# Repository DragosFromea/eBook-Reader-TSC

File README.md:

| Component               | Supplier Link                                                                 | Datasheet                                                                 |
|-------------------------|-------------------------------------------------------------------------------|---------------------------------------------------------------------------|
| 112A-TAAR-R03 ATTEND    | -| [Datasheet](https://www.snapeda.com/parts/112A-TAAR-R03/Attend/datasheet/)|
| BD5229G-TR              | [Mouser](https://www.mouser.co.uk/ProductDetail/ROHM-Semiconductor/BD5229G-TR?qs=4kLU8WoGk0vvnhrrYwdszw%3D%3D)| [Datasheet](https://fscdn.rohm.com/en/products/databook/datasheet/ic/power/voltage_detector/bd52xxg-e.pdf) |
| CPH3225A (Supercapacitor)| [SnapEDA](https://www.snapeda.com/parts/CPH3225A/Seiko+Instruments/view-part/?ref=eda) | [Datasheet](https://www.snapeda.com/parts/CPH3225A/Seiko%20Instruments/datasheet/) |
| DS3231SN# (RTC)         | [SnapEDA](https://www.snapeda.com/parts/DS3231SN%23/Analog+Devices/view-part/?ref=eda) | [Datasheet](https://www.analog.com/media/en/technical-documentation/data-sheets/DS3231.pdf) |
| ESP32-C6-WROOM-1-N8     | [SnapEDA](https://www.snapeda.com/parts/ESP32-C6-WROOM-1-N8/Espressif+Systems/view-part/?ref=eda) | [Datasheet](https://www.espressif.com/sites/default/files/documentation/esp32-c6-wroom-1_datasheet_en.pdf) |
| FH34SRJ-24S-0.5SH99     | [Mouser](https://ro.mouser.com/ProductDetail/Hirose-Connector/FH34SRJ-24S-0.5SH99?qs=vcbW%252B4%252BSTIpKBl5ap9J8Fw%3D%3D) | [Datasheet](https://www.hirose.com/product/document?clcode=CL0537-0513-9-10&productname=FH34SRJ-24S-0.5SH(99)&series=FH34&documenttype=Catalog&lang=en&documentid=D31688_en) |
| MBR0530 (Schottky Diode)| [SnapEDA](https://www.snapeda.com/parts/MBR0530/Onsemi/view-part/?ref=eda)                 | [Datasheet](https://www.onsemi.com/pdf/datasheet/mbr0530-d.pdf)           |
| MAX17048G+T10 (Fuel Gauge)| [SnapEDA](https://www.snapeda.com/parts/MAX17048G+T10/Analog+Devices/view-part/?ref=eda)| [Datasheet](https://www.analog.com/media/en/technical-documentation/data-sheets/MAX17048-MAX17049.pdf) |
| USBLC6-2SC6Y (TVS Diode)| [SnapEDA](https://www.snapeda.com/parts/USBLC6-2SC6Y/STMicroelectronics/view-part/?ref=eda)| [Datasheet](https://www.st.com/resource/en/datasheet/usblc6-2.pdf) |
| W25Q512JVEIQ (Flash)    | [SnapEDA](https://www.snapeda.com/parts/W25Q512JVEIQ/Winbond+Electronics/view-part/?ref=eda)| [Datasheet](https://www.winbond.com/resource-files/W25Q512JV%20SPI%20RevB%2006252019%20KMS.pdf) |
| XC6220A331MR-G (LDO)    | [Mouser](https://www.mouser.co.uk/ProductDetail/Torex-Semiconductor/XC6220A331MR-G?qs=AsjdqWjXhJ8ZSWznL1J0gg%3D%3D)| [Datasheet](https://product.torexsemi.com/system/files/series/xc6220.pdf) |                                                                         |
| QWIIC Connector          | -                           | [Datasheet](https://learn.sparkfun.com/tutorials/qwiic-shield-for-arduino--photon-hookup-guide) |

Core Components
Microcontroller (ESP32-C6-WROOM-1-N8):

    Architecture: 32-bit RISC-V

    Clock Speed: 160 MHz

    Wireless: Wi-Fi 6 (2.4 GHz), Bluetooth 5.0

    Functions: System control, sensor/module communication, power management.

Power Management
Battery System:

    Type: Li-Po (Lithium Polymer)

    Capacity: 3.7V, 1800mAh

    Charging Circuit: MCP73831T (5V input via USB-C)

    Protection: Overcharge and deep discharge safeguards.

    Voltage Regulation: LDO regulator (stable 3.3V output).

Storage & Display
E-Paper Display:

    Size: 7.5 inches | Resolution: 800×480 pixels

    Interface: SPI

MicroSD Card Module:

    Format: FAT32 | Interface: SPI

External NOR Flash:

    Capacity: 64MB | Interface: SPI

Sensors & Timing
Environmental Sensor (BME688):

    Metrics: Temperature, humidity, air pressure, gas levels.

    Interface: I2C

Real-Time Clock (DS3231SN):

    Function: Maintains time/date during power loss.

    Interface: I2C

User Interface
USB-C Connector:

    Role: Power input, data transfer.

    Safety: ESD protection + Schottky diode (reverse polarity).

Tactile Push Buttons:

    Control: GPIO-based input.

Communication Interfaces
SPI: SD card, external flash, e-paper display.

I2C: BME688 sensor, DS3231SN RTC.

GPIO: Button controls, general I/O.

UART: Debugging, serial communication.

Wireless: Wi-Fi 6/Bluetooth 5.0 (via ESP32-C6).

### Power Consumption Estimation  
| Component                      | Current Draw (mA) | Voltage (V) | Power (mW) |  
|--------------------------------|-------------------|-------------|------------|  
| ESP32-C6 (Wi-Fi active)        | 200               | 3.3         | 660        |  
| E-Paper Display (Updating)     | 40                | 3.3         | 132        |  
| BME688 Sensor (Measuring)      | 3.1               | 3.3         | 10.23      |  
| RTC Module (Active)            | 0.15              | 3.3         | 0.495      |  
| SD Card (Active)               | 50                | 3.3         | 165        |  
| External NOR Flash             | 25                | 3.3         | 82.5       |  
| **Total Estimated Power Consumption** | **~318.5 mA**     | **3.3**     | **1050.72**|  

---

### ESP32-C6 Pin Mapping  
| Component                      | ESP32-C6 Pin(s)                                | Interface | Purpose                                                                 |  
|--------------------------------|------------------------------------------------|-----------|-------------------------------------------------------------------------|  
| E-Paper Display                | IO7 (MOSI), IO6 (SCK), IO10 (CS), IO5 (DC), IO23 (RST), IO3 (BUSY) | SPI       | Transfers image data to the display and controls its state.             |  
| MicroSD Card                   | IO7 (MOSI), IO6 (SCK), IO4 (SS_SD), IO2 (MISO) | SPI       | Storage and retrieval of e-book files.                                  |  
| Environmental Sensor (BME688)  | IO21 (SDA), IO22 (SCL)                         | I2C       | Reads temperature, humidity, pressure, and air quality data.            |  
| RTC Module (DS3231)            | IO21 (SDA), IO22 (SCL), IO18 (RST), IO1 (32KHz), IO0 (INT_RTC) | I2C       | Maintains time/date tracking during system power-off.                   |  
| External NOR Flash             | IO11 (CS), IO6 (SCK), IO2 (MISO), IO7 (MOSI)   | SPI       | Additional storage for application data.                                |  
| Battery Monitoring             | IO21 (SDA), IO22 (SCL)                         | I2C       | Monitors battery voltage and charge status.                             |  
| USB-C Connection               | GPIOs (via voltage regulation)                 | USB       | Powers and programs the ESP32-C6.                                       |  
| Control Buttons                | IO9 (BOOT), IO15 (CHANGE), EN (RESET)          | GPIO      | User input for device interactions (boot, mode change, reset).          |  

Am acceptat erorile SMD de overlap

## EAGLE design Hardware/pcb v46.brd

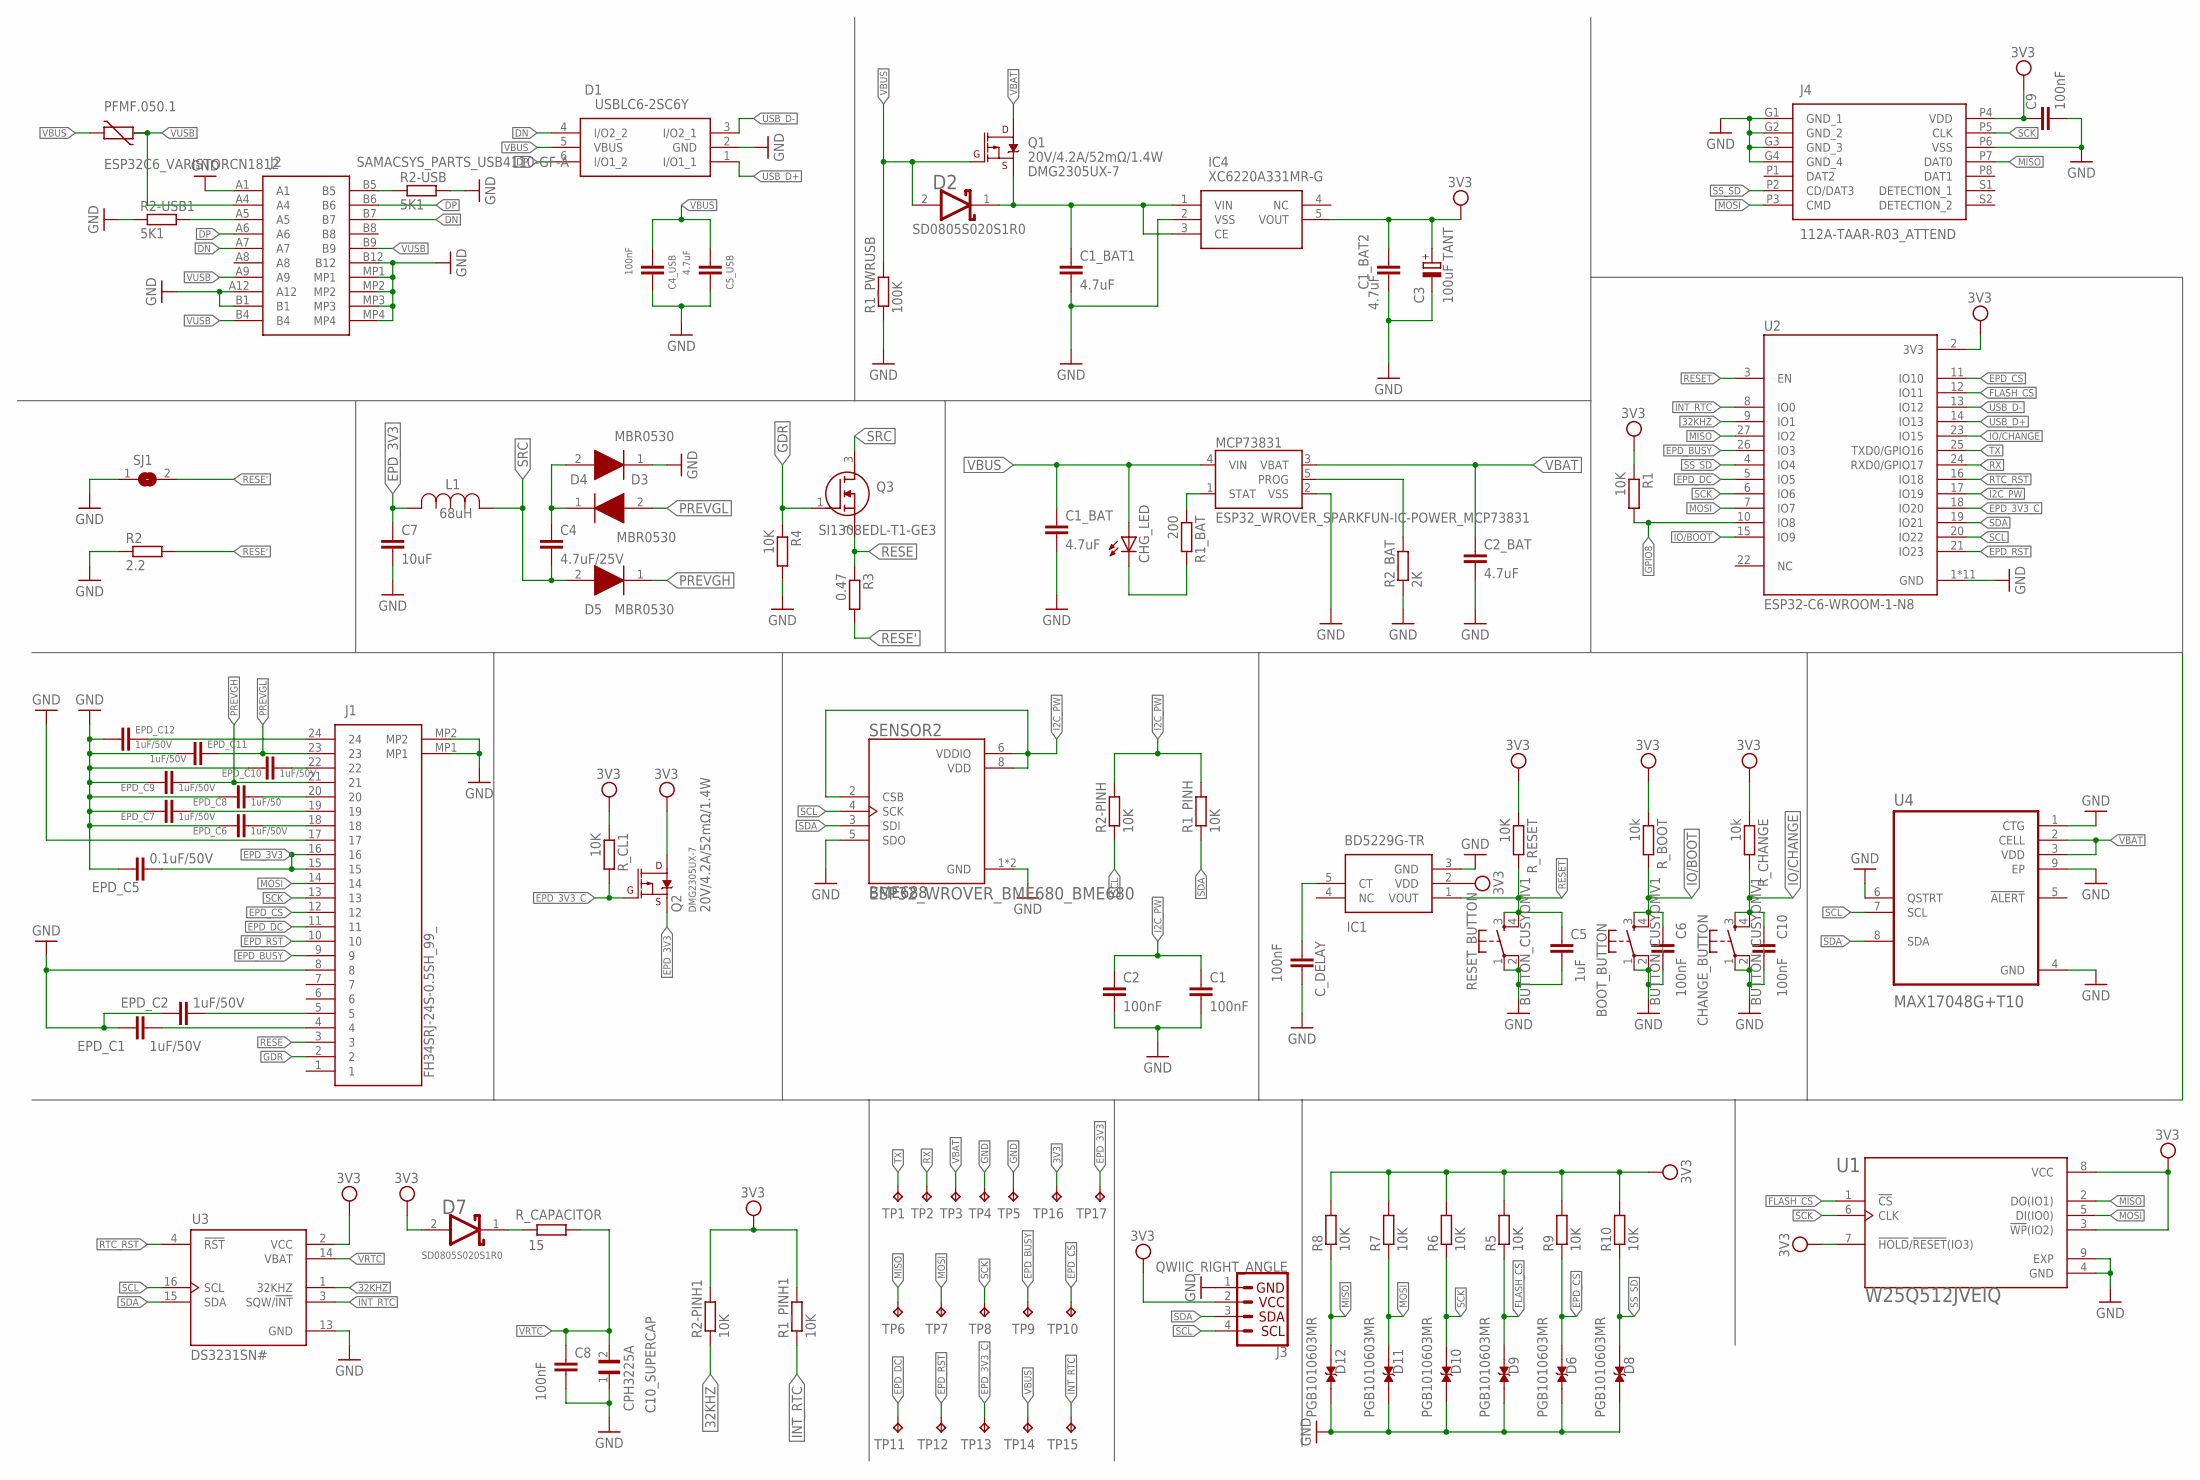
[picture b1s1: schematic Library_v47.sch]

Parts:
BOOT_BUTTON: BUTTON_CUSYOMV1; MYBUTTON
C1, C2, C4_USB, C6, C8, C9, C10: 100nF; ESP32_WROVER_EAGLE-LTSPICE_C0402
C1_BAT, C1_BAT1, C1_BAT2, C2_BAT, C5_USB: 4.7uF; ESP32_WROVER_EAGLE-LTSPICE_C0402
C3: 100uF TANT; RCL_CT3528
C4: 4.7uF/25V; ESP32_WROVER_EAGLE-LTSPICE_C0402
C5: 1uF; ESP32_WROVER_EAGLE-LTSPICE_C0402
C7: 10uF; ESP32_WROVER_EAGLE-LTSPICE_C0402
C10_SUPERCAP: CPH3225A; CAPCP3225X100N
CHANGE_BUTTON: BUTTON_CUSYOMV1; MYBUTTON
CHG_LED: ADAFRUIT_LEDCHIP-LED0603; ADAFRUIT_CHIP-LED0603
C_DELAY: 100nF; ESP32_WROVER_EAGLE-LTSPICE_C0402
D1: USBLC6-2SC6Y; SOT95P280X145-6N
D2, D7: ESP32_WROVER_AVX---SD0805S020S1R0_AVX_SD0805S020S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; ESP32_WROVER_AVX---SD0805S020S1R0_AVX_SD0805S020S1R0_0
D3, D4, D5: MBR0530; SOD3716X135N
D6, D8, D9, D10, D11, D12: PGB1010603MR; DIOC1608X36N
EPD_C1, EPD_C2, EPD_C6, EPD_C7, EPD_C9, EPD_C10, EPD_C11, EPD_C12: 1uF/50V; ESP32_WROVER_EAGLE-LTSPICE_C0402
EPD_C5: 0.1uF/50V; ESP32_WROVER_EAGLE-LTSPICE_C0402
EPD_C8: 1uF/50; ESP32_WROVER_EAGLE-LTSPICE_C0402
IC1: BD5229G-TR; SOT95P280X125-5N
IC4: XC6220A331MR-G; SOT95P280X120-5N
J1: FH34SRJ-24S-0.5SH_99_; FH34SRJ24S05SH99
J2: SAMACSYS_PARTS_USB4110-GF-A; SAMACSYS_PARTS_USB4110GFA
J3: QWIIC_RIGHT_ANGLE; JST04_1MM_RA
J4: 112A-TAAR-R03_ATTEND; 112ATAARR03ATTEND
L1: 68uH; IND_4828-WE-TPC_WRE
MCP73831: ESP32_WROVER_SPARKFUN-IC-POWER_MCP73831; ESP32_WROVER_SPARKFUN-IC-POWER_SOT23-5
PFMF.050.1: ESP32C6_VARISTORCN1812; ESP32C6_VARISTOR_CT/CN1812
Q1, Q2: 20V/4.2A/52mΩ/1.4W; ESP32_WROVER_SPARKFUN-DISCRETESEMI_SOT23-3
Q3: SI1308EDL-T1-GE3; SOT65P210X110-3N
R1, R1_PINH, R1_PINH1, R2-PINH, R2-PINH1, R4, R5, R6, R7, R8, R9, R10: 10K; ESP32_WROVER_EAGLE-LTSPICE_R0402
R1_BAT: 200; ESP32_WROVER_EAGLE-LTSPICE_R0402
R1_PWRUSB: 100K; ESP32_WROVER_EAGLE-LTSPICE_R0402
R2: 2.2; ESP32_WROVER_EAGLE-LTSPICE_R0402
R2-USB, R2-USB1: 5K1; ESP32_WROVER_EAGLE-LTSPICE_R0402
R2_BAT: 2K; ESP32_WROVER_EAGLE-LTSPICE_R0402
R3: 0.47; ESP32_WROVER_EAGLE-LTSPICE_R0402
RESET_BUTTON: BUTTON_CUSYOMV1; MYBUTTON
R_BOOT: 10k; ESP32_WROVER_EAGLE-LTSPICE_R0402
R_CAPACITOR: 15; ESP32_WROVER_EAGLE-LTSPICE_R0402
R_CHANGE: 10k; ESP32_WROVER_EAGLE-LTSPICE_R0402
R_CL1: 10K; ESP32_WROVER_EAGLE-LTSPICE_R0402
R_RESET: 10K; ESP32_WROVER_EAGLE-LTSPICE_R0402
SENSOR2: ESP32_WROVER_BME680_BME680; ESP32_WROVER_BME680_PSON80P300X300X100-8N
SJ1: SJ
TP1, TP2, TP3, TP4, TP5, TP6, TP7, TP8, TP9, TP10, TP11, TP12, TP13, TP14, TP15, TP16, TP17: TPTP20R; TP20R
U1: W25Q512JVEIQ; SON127P600X800X80-9N
U2: ESP32-C6-WROOM-1-N8; XCVR_ESP32-C6-WROOM-1-N8
U3: DS3231SN#; SOIC127P1032X265-16N
U4: MAX17048G+T10; SON50P200X200X80-9N

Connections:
3V3: C1_BAT2.1, C3.+, C9.1, D7.2 (ANODE), IC1.2 (VDD), IC4.5 (VOUT), J3.2, J4.P4 (VDD), Q2.3 (D), R1.1, R1_PINH1.2, R2-PINH1.2, R5.2, R6.2, R7.2, R8.2, R9.2, R10.2, R_BOOT.1, R_CHANGE.1, R_CL1.1, R_RESET.1, TP16.TP, U1.3 (!WP!(IO2)), U1.7 (!HOLD!/!RESET!(IO3)), U1.8 (VCC), U2.2 (3V3), U3.2 (VCC)
32KHZ: R2-PINH1.1, U2.9 (IO1), U3.1 (32KHZ)
DN: D1.4 (I/O2_2), J2.A7, J2.B7
DP: D1.6 (I/O1_2), J2.A6, J2.B6
EPD_3V3: C7.1, EPD_C5.1, J1.15, J1.16, L1.2, Q2.2 (S), TP17.TP
EPD_3V3_C: Q2.1 (G), R_CL1.2, TP13.TP, U2.18 (IO20)
EPD_BUSY: J1.9, TP9.TP, U2.26 (IO3)
EPD_CS: D6.2, J1.12, R9.1, TP10.TP, U2.11 (IO10)
EPD_DC: J1.11, TP11.TP, U2.5 (IO5)
EPD_RST: J1.10, TP12.TP, U2.21 (IO23)
FLASH_CS: D9.2, R5.1, U1.1 (!CS), U2.12 (IO11)
GDR: J1.2, Q3.1 (G), R4.1
GND: BOOT_BUTTON.1, BOOT_BUTTON.2, C1.2, C1_BAT.2, C1_BAT1.2, C1_BAT2.2, C2.2, C2_BAT.2, C3.-, C4_USB.2, C5.2, C5_USB.2, C6.2, C7.2, C8.2, C9.2, C10.2, C10_SUPERCAP.1, CHANGE_BUTTON.1, CHANGE_BUTTON.2, C_DELAY.2, D1.2 (GND), D4.1 (K), D6.1, D8.1, D9.1, D10.1, D11.1, D12.1, EPD_C1.2, EPD_C2.2, EPD_C5.2, EPD_C6.2, EPD_C7.2, EPD_C8.2, EPD_C9.2, EPD_C10.2, EPD_C11.2, EPD_C12.2, IC1.3 (GND), IC4.2 (VSS), J1.8, J1.17, J1.MP1, J1.MP2, J2.A1, J2.A12, J2.B1, J2.B12, J2.MP1, J2.MP2, J2.MP3, J2.MP4, J3.1, J4.G1 (GND_1), J4.G2 (GND_2), J4.G3 (GND_3), J4.G4 (GND_4), J4.P6 (VSS), MCP73831.2 (VSS), R1_PWRUSB.1, R2.1, R2-USB.2, R2-USB1.1, R2_BAT.1, R4.2, RESET_BUTTON.1, RESET_BUTTON.2, SENSOR2.1 (GND), SENSOR2.5 (SDO), SENSOR2.7 (GND), SJ1.1, TP4.TP, TP5.TP, U1.4 (GND), U1.9 (EXP), U2.1 (GND), U2.28 (GND), U2.29_1 (GND), U2.29_2 (GND), U2.29_3 (GND), U2.29_4 (GND), U2.29_5 (GND), U2.29_6 (GND), U2.29_7 (GND), U2.29_8 (GND), U2.29_9 (GND), U3.13 (GND), U4.1 (CTG), U4.4 (GND), U4.6 (QSTRT), U4.9 (EP)
GPIO8: R1.2, U2.10 (IO8)
I2C_PW: C1.1, C2.1, R1_PINH.2, R2-PINH.2, SENSOR2.2 (CSB), SENSOR2.6 (VDDIO), SENSOR2.8 (VDD), U2.17 (IO19)
INT_RTC: R1_PINH1.1, TP15.TP, U2.8 (IO0), U3.3 (SQW/!INT)
IO/BOOT: BOOT_BUTTON.3, BOOT_BUTTON.4, C6.1, R_BOOT.2, U2.15 (IO9)
IO/CHANGE: C10.1, CHANGE_BUTTON.3, CHANGE_BUTTON.4, R_CHANGE.2, U2.23 (IO15)
MISO: D12.2, J4.P7 (DAT0), R8.1, TP6.TP, U1.2 (DO(IO1)), U2.27 (IO2)
MOSI: D11.2, J1.14, J4.P3 (CMD), R7.1, TP7.TP, U1.5 (DI(IO0)), U2.7 (IO7)
unnamed: C1_BAT1.1, D2.1 (CATHODE), IC4.1 (VIN), IC4.3 (CE), Q1.2 (S)
unnamed: J2.B5, R2-USB.1
unnamed: J2.A5, R2-USB1.2
unnamed: MCP73831.1 (STAT), R1_BAT.1
unnamed: C4.1, D3.1 (K), D4.2 (A)
unnamed: CHG_LED.C, R1_BAT.2
unnamed: MCP73831.5 (PROG), R2_BAT.2
unnamed: EPD_C1.1, J1.4
unnamed: EPD_C2.1, J1.5
unnamed: EPD_C6.1, J1.18
unnamed: EPD_C7.1, J1.19
unnamed: EPD_C8.1, J1.20
unnamed: EPD_C10.1, J1.22
unnamed: C_DELAY.1, IC1.5 (CT)
unnamed: EPD_C12.1, J1.24
unnamed: D7.1 (CATHODE), R_CAPACITOR.2
PREVGH: D5.1 (K), EPD_C9.1, J1.21
PREVGL: D3.2 (A), EPD_C11.1, J1.23
RESE: J1.3, Q3.2 (S), R3.1
RESE': R2.2, R3.2, SJ1.2
RESET: C5.1, IC1.1 (VOUT), RESET_BUTTON.3, RESET_BUTTON.4, R_RESET.2, U2.3 (EN)
RTC_RST: U2.16 (IO18), U3.4 (!RST)
RX: TP2.TP, U2.24 (RXD0/GPIO17)
SCK: D10.2, J1.13, J4.P5 (CLK), R6.1, TP8.TP, U1.6 (CLK), U2.6 (IO6)
SCL: J3.4, R2-PINH.1, SENSOR2.4 (SCK), U2.20 (IO22), U3.16 (SCL), U4.7 (SCL)
SDA: J3.3, R1_PINH.1, SENSOR2.3 (SDI), U2.19 (IO21), U3.15 (SDA), U4.8 (SDA)
SRC: C4.2, D5.2 (A), L1.1, Q3.3 (D)
SS_SD: D8.2, J4.P2 (CD/DAT3), R10.1, U2.4 (IO4)
TX: TP1.TP, U2.25 (TXD0/GPIO16)
USB_D+: D1.1 (I/O1_1), U2.14 (IO13)
USB_D-: D1.3 (I/O2_1), U2.13 (IO12)
VBAT: C2_BAT.1, MCP73831.3 (VBAT), Q1.3 (D), TP3.TP, U4.2 (CELL), U4.3 (VDD)
VBUS: C1_BAT.1, C4_USB.1, C5_USB.1, CHG_LED.A, D1.5 (VBUS), D2.2 (ANODE), MCP73831.4 (VIN), PFMF.050.1.2, Q1.1 (G), R1_PWRUSB.2, TP14.TP
VRTC: C8.1, C10_SUPERCAP.2, R_CAPACITOR.1, U3.14 (VBAT)
VUSB: J2.A4, J2.A9, J2.B4, J2.B9, PFMF.050.1.1

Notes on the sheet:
DMG2305UX-7
SD0805S020S1R0
BME688

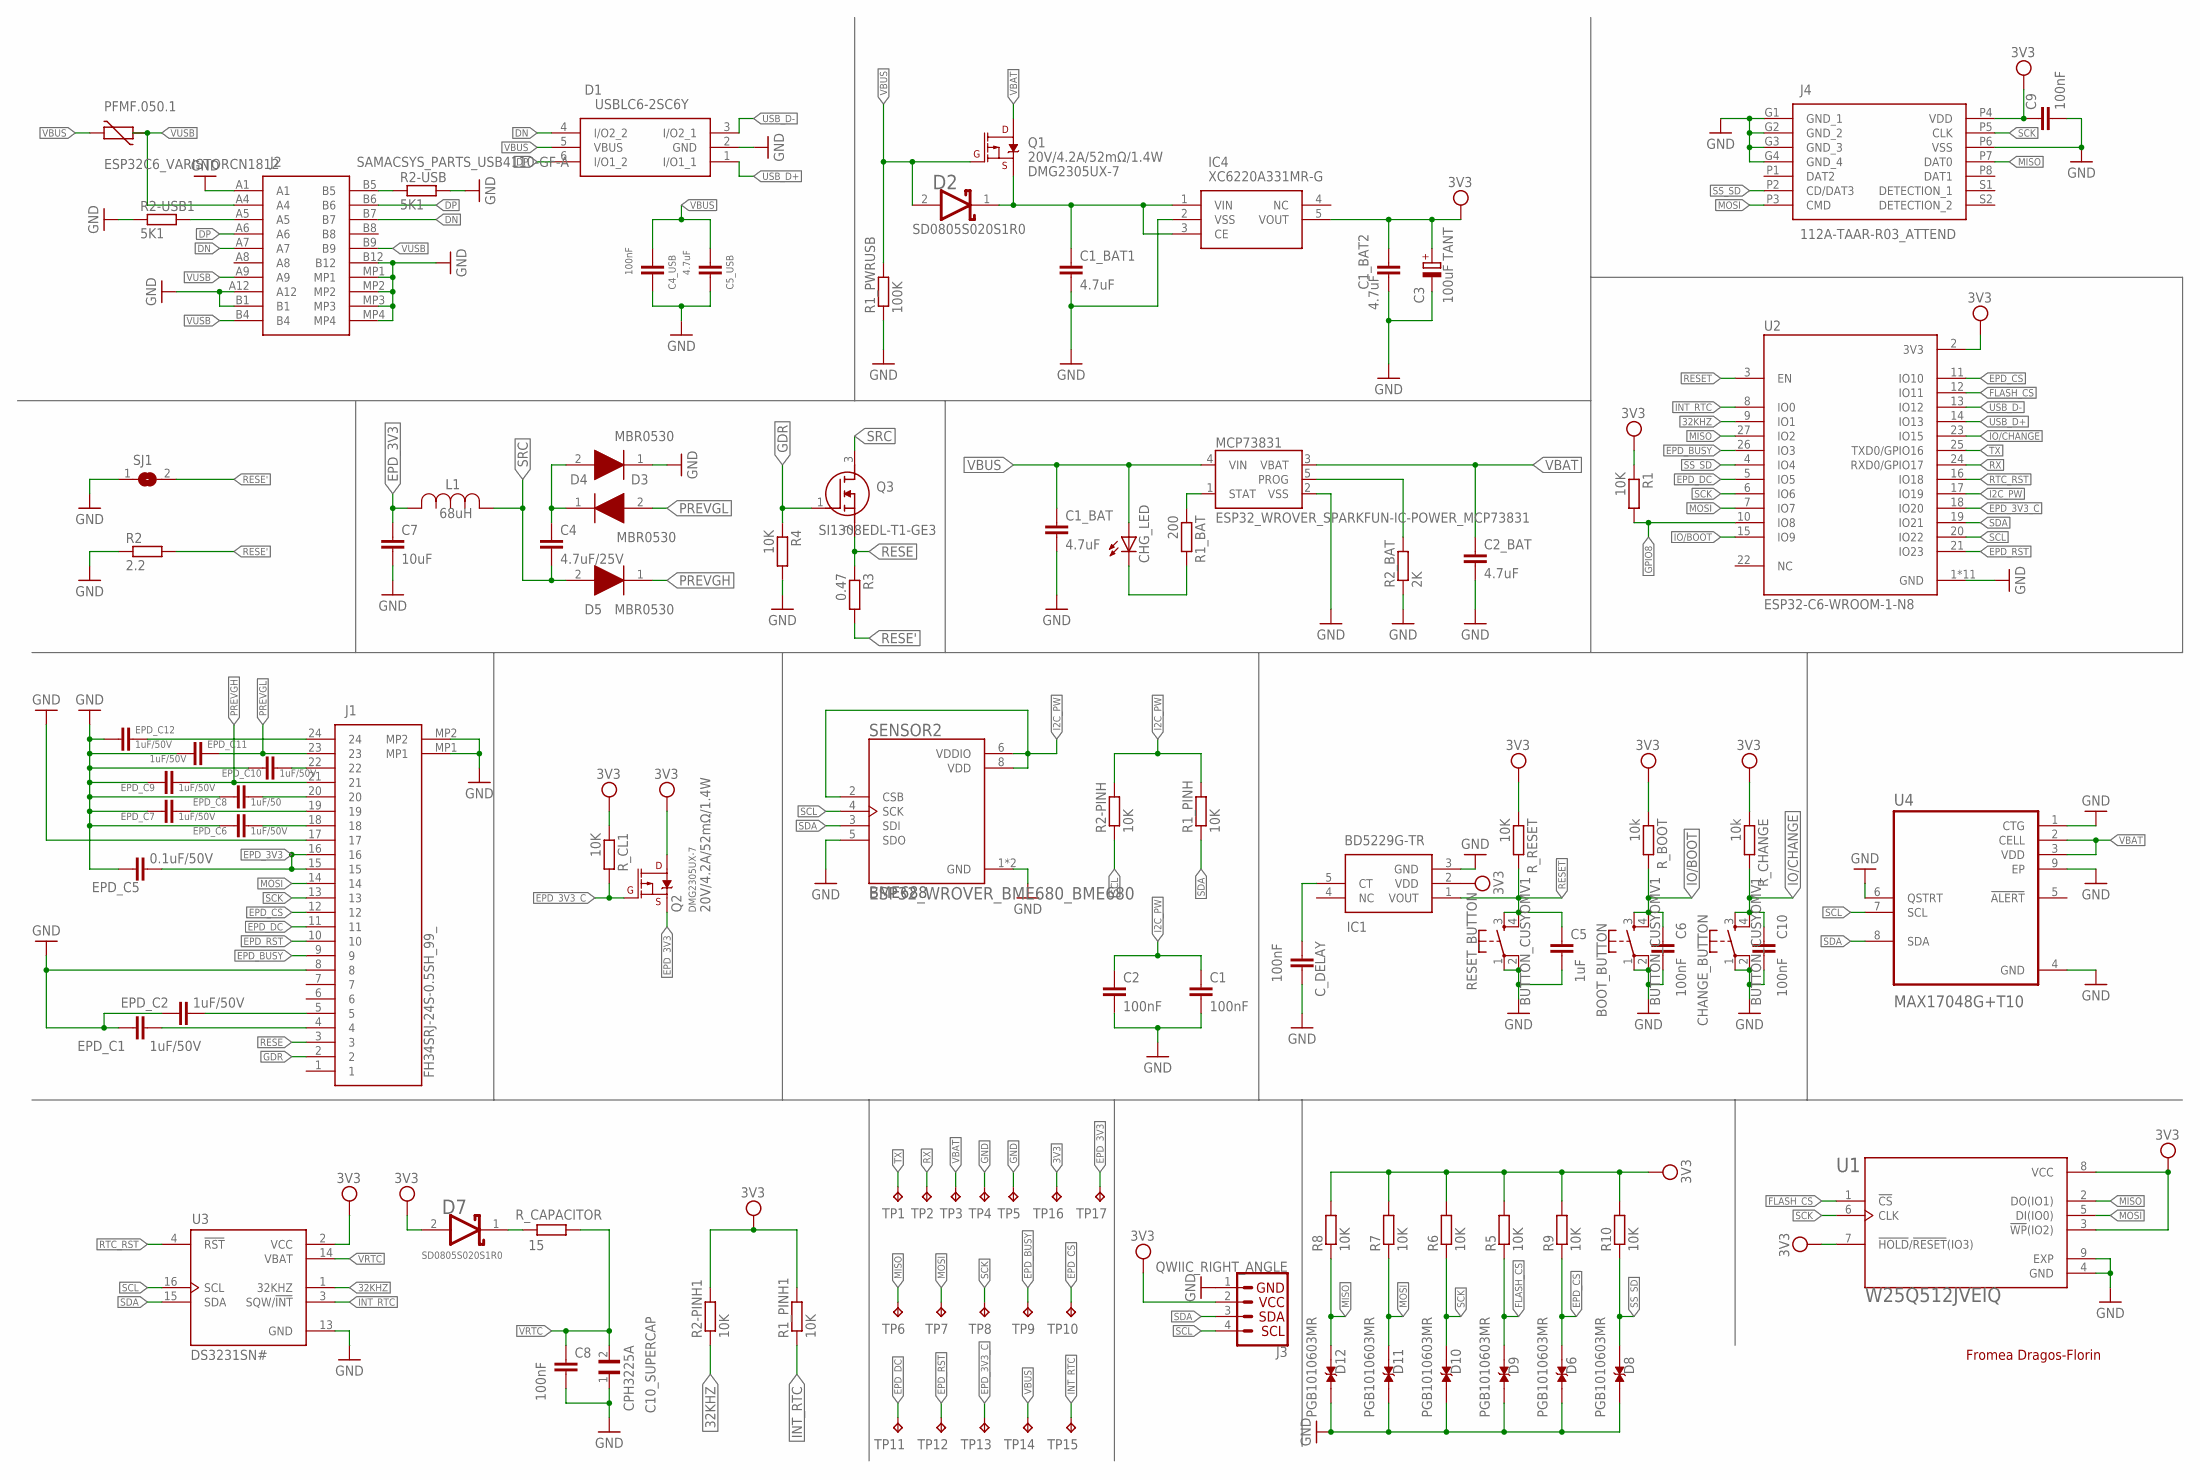
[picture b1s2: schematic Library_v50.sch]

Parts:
BOOT_BUTTON: BUTTON_CUSYOMV1; MYBUTTON
C1, C2, C4_USB, C6, C8, C9, C10: 100nF; ESP32_WROVER_EAGLE-LTSPICE_C0402
C1_BAT, C1_BAT1, C1_BAT2, C2_BAT, C5_USB: 4.7uF; ESP32_WROVER_EAGLE-LTSPICE_C0402
C3: 100uF TANT; RCL_CT3528
C4: 4.7uF/25V; ESP32_WROVER_EAGLE-LTSPICE_C0402
C5: 1uF; ESP32_WROVER_EAGLE-LTSPICE_C0402
C7: 10uF; ESP32_WROVER_EAGLE-LTSPICE_C0402
C10_SUPERCAP: CPH3225A; CAPCP3225X100N
CHANGE_BUTTON: BUTTON_CUSYOMV1; MYBUTTON
CHG_LED: ADAFRUIT_LEDCHIP-LED0603; ADAFRUIT_CHIP-LED0603
C_DELAY: 100nF; ESP32_WROVER_EAGLE-LTSPICE_C0402
D1: USBLC6-2SC6Y; SOT95P280X145-6N
D2, D7: ESP32_WROVER_AVX---SD0805S020S1R0_AVX_SD0805S020S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; ESP32_WROVER_AVX---SD0805S020S1R0_AVX_SD0805S020S1R0_0
D3, D4, D5: MBR0530; SOD3716X135N
D6, D8, D9, D10, D11, D12: PGB1010603MR; DIOC1608X36N
EPD_C1, EPD_C2, EPD_C6, EPD_C7, EPD_C9, EPD_C10, EPD_C11, EPD_C12: 1uF/50V; ESP32_WROVER_EAGLE-LTSPICE_C0402
EPD_C5: 0.1uF/50V; ESP32_WROVER_EAGLE-LTSPICE_C0402
EPD_C8: 1uF/50; ESP32_WROVER_EAGLE-LTSPICE_C0402
IC1: BD5229G-TR; SOT95P280X125-5N
IC4: XC6220A331MR-G; SOT95P280X120-5N
J1: FH34SRJ-24S-0.5SH_99_; FH34SRJ24S05SH99
J2: SAMACSYS_PARTS_USB4110-GF-A; SAMACSYS_PARTS_USB4110GFA
J3: QWIIC_RIGHT_ANGLE; JST04_1MM_RA
J4: 112A-TAAR-R03_ATTEND; 112ATAARR03ATTEND
L1: 68uH; IND_4828-WE-TPC_WRE
MCP73831: ESP32_WROVER_SPARKFUN-IC-POWER_MCP73831; ESP32_WROVER_SPARKFUN-IC-POWER_SOT23-5
PFMF.050.1: ESP32C6_VARISTORCN1812; ESP32C6_VARISTOR_CT/CN1812
Q1, Q2: 20V/4.2A/52mΩ/1.4W; ESP32_WROVER_SPARKFUN-DISCRETESEMI_SOT23-3
Q3: SI1308EDL-T1-GE3; SOT65P210X110-3N
R1, R1_PINH, R1_PINH1, R2-PINH, R2-PINH1, R4, R5, R6, R7, R8, R9, R10: 10K; ESP32_WROVER_EAGLE-LTSPICE_R0402
R1_BAT: 200; ESP32_WROVER_EAGLE-LTSPICE_R0402
R1_PWRUSB: 100K; ESP32_WROVER_EAGLE-LTSPICE_R0402
R2: 2.2; ESP32_WROVER_EAGLE-LTSPICE_R0402
R2-USB, R2-USB1: 5K1; ESP32_WROVER_EAGLE-LTSPICE_R0402
R2_BAT: 2K; ESP32_WROVER_EAGLE-LTSPICE_R0402
R3: 0.47; ESP32_WROVER_EAGLE-LTSPICE_R0402
RESET_BUTTON: BUTTON_CUSYOMV1; MYBUTTON
R_BOOT: 10k; ESP32_WROVER_EAGLE-LTSPICE_R0402
R_CAPACITOR: 15; ESP32_WROVER_EAGLE-LTSPICE_R0402
R_CHANGE: 10k; ESP32_WROVER_EAGLE-LTSPICE_R0402
R_CL1: 10K; ESP32_WROVER_EAGLE-LTSPICE_R0402
R_RESET: 10K; ESP32_WROVER_EAGLE-LTSPICE_R0402
SENSOR2: ESP32_WROVER_BME680_BME680; ESP32_WROVER_BME680_PSON80P300X300X100-8N
SJ1: SJ
TP1, TP2, TP3, TP4, TP5, TP6, TP7, TP8, TP9, TP10, TP11, TP12, TP13, TP14, TP15, TP16, TP17: TPTP20R; TP20R
U1: W25Q512JVEIQ; SON127P600X800X80-9N
U2: ESP32-C6-WROOM-1-N8; XCVR_ESP32-C6-WROOM-1-N8
U3: DS3231SN#; SOIC127P1032X265-16N
U4: MAX17048G+T10; SON50P200X200X80-9N

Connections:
3V3: C1_BAT2.1, C3.+, C9.1, D7.2 (ANODE), IC1.2 (VDD), IC4.5 (VOUT), J3.2, J4.P4 (VDD), Q2.3 (D), R1.1, R1_PINH1.2, R2-PINH1.2, R5.2, R6.2, R7.2, R8.2, R9.2, R10.2, R_BOOT.1, R_CHANGE.1, R_CL1.1, R_RESET.1, TP16.TP, U1.3 (!WP!(IO2)), U1.7 (!HOLD!/!RESET!(IO3)), U1.8 (VCC), U2.2 (3V3), U3.2 (VCC)
32KHZ: R2-PINH1.1, U2.9 (IO1), U3.1 (32KHZ)
DN: D1.4 (I/O2_2), J2.A7, J2.B7
DP: D1.6 (I/O1_2), J2.A6, J2.B6
EPD_3V3: C7.1, EPD_C5.1, J1.15, J1.16, L1.2, Q2.2 (S), TP17.TP
EPD_3V3_C: Q2.1 (G), R_CL1.2, TP13.TP, U2.18 (IO20)
EPD_BUSY: J1.9, TP9.TP, U2.26 (IO3)
EPD_CS: D6.2, J1.12, R9.1, TP10.TP, U2.11 (IO10)
EPD_DC: J1.11, TP11.TP, U2.5 (IO5)
EPD_RST: J1.10, TP12.TP, U2.21 (IO23)
FLASH_CS: D9.2, R5.1, U1.1 (!CS), U2.12 (IO11)
GDR: J1.2, Q3.1 (G), R4.1
GND: BOOT_BUTTON.1, BOOT_BUTTON.2, C1.2, C1_BAT.2, C1_BAT1.2, C1_BAT2.2, C2.2, C2_BAT.2, C3.-, C4_USB.2, C5.2, C5_USB.2, C6.2, C7.2, C8.2, C9.2, C10.2, C10_SUPERCAP.1, CHANGE_BUTTON.1, CHANGE_BUTTON.2, C_DELAY.2, D1.2 (GND), D4.1 (K), D6.1, D8.1, D9.1, D10.1, D11.1, D12.1, EPD_C1.2, EPD_C2.2, EPD_C5.2, EPD_C6.2, EPD_C7.2, EPD_C8.2, EPD_C9.2, EPD_C10.2, EPD_C11.2, EPD_C12.2, IC1.3 (GND), IC4.2 (VSS), J1.8, J1.17, J1.MP1, J1.MP2, J2.A1, J2.A12, J2.B1, J2.B12, J2.MP1, J2.MP2, J2.MP3, J2.MP4, J3.1, J4.G1 (GND_1), J4.G2 (GND_2), J4.G3 (GND_3), J4.G4 (GND_4), J4.P6 (VSS), MCP73831.2 (VSS), R1_PWRUSB.1, R2.1, R2-USB.2, R2-USB1.1, R2_BAT.1, R4.2, RESET_BUTTON.1, RESET_BUTTON.2, SENSOR2.1 (GND), SENSOR2.5 (SDO), SENSOR2.7 (GND), SJ1.1, TP4.TP, TP5.TP, U1.4 (GND), U1.9 (EXP), U2.1 (GND), U2.28 (GND), U2.29_1 (GND), U2.29_2 (GND), U2.29_3 (GND), U2.29_4 (GND), U2.29_5 (GND), U2.29_6 (GND), U2.29_7 (GND), U2.29_8 (GND), U2.29_9 (GND), U3.13 (GND), U4.1 (CTG), U4.4 (GND), U4.6 (QSTRT), U4.9 (EP)
GPIO8: R1.2, U2.10 (IO8)
I2C_PW: C1.1, C2.1, R1_PINH.2, R2-PINH.2, SENSOR2.2 (CSB), SENSOR2.6 (VDDIO), SENSOR2.8 (VDD), U2.17 (IO19)
INT_RTC: R1_PINH1.1, TP15.TP, U2.8 (IO0), U3.3 (SQW/!INT)
IO/BOOT: BOOT_BUTTON.3, BOOT_BUTTON.4, C6.1, R_BOOT.2, U2.15 (IO9)
IO/CHANGE: C10.1, CHANGE_BUTTON.3, CHANGE_BUTTON.4, R_CHANGE.2, U2.23 (IO15)
MISO: D12.2, J4.P7 (DAT0), R8.1, TP6.TP, U1.2 (DO(IO1)), U2.27 (IO2)
MOSI: D11.2, J1.14, J4.P3 (CMD), R7.1, TP7.TP, U1.5 (DI(IO0)), U2.7 (IO7)
unnamed: C1_BAT1.1, D2.1 (CATHODE), IC4.1 (VIN), IC4.3 (CE), Q1.2 (S)
unnamed: J2.B5, R2-USB.1
unnamed: J2.A5, R2-USB1.2
unnamed: MCP73831.1 (STAT), R1_BAT.1
unnamed: C4.1, D3.1 (K), D4.2 (A)
unnamed: CHG_LED.C, R1_BAT.2
unnamed: MCP73831.5 (PROG), R2_BAT.2
unnamed: EPD_C1.1, J1.4
unnamed: EPD_C2.1, J1.5
unnamed: EPD_C6.1, J1.18
unnamed: EPD_C7.1, J1.19
unnamed: EPD_C8.1, J1.20
unnamed: EPD_C10.1, J1.22
unnamed: C_DELAY.1, IC1.5 (CT)
unnamed: EPD_C12.1, J1.24
unnamed: D7.1 (CATHODE), R_CAPACITOR.2
PREVGH: D5.1 (K), EPD_C9.1, J1.21
PREVGL: D3.2 (A), EPD_C11.1, J1.23
RESE: J1.3, Q3.2 (S), R3.1
RESE': R2.2, R3.2, SJ1.2
RESET: C5.1, IC1.1 (VOUT), RESET_BUTTON.3, RESET_BUTTON.4, R_RESET.2, U2.3 (EN)
RTC_RST: U2.16 (IO18), U3.4 (!RST)
RX: TP2.TP, U2.24 (RXD0/GPIO17)
SCK: D10.2, J1.13, J4.P5 (CLK), R6.1, TP8.TP, U1.6 (CLK), U2.6 (IO6)
SCL: J3.4, R2-PINH.1, SENSOR2.4 (SCK), U2.20 (IO22), U3.16 (SCL), U4.7 (SCL)
SDA: J3.3, R1_PINH.1, SENSOR2.3 (SDI), U2.19 (IO21), U3.15 (SDA), U4.8 (SDA)
SRC: C4.2, D5.2 (A), L1.1, Q3.3 (D)
SS_SD: D8.2, J4.P2 (CD/DAT3), R10.1, U2.4 (IO4)
TX: TP1.TP, U2.25 (TXD0/GPIO16)
USB_D+: D1.1 (I/O1_1), U2.14 (IO13)
USB_D-: D1.3 (I/O2_1), U2.13 (IO12)
VBAT: C2_BAT.1, MCP73831.3 (VBAT), Q1.3 (D), TP3.TP, U4.2 (CELL), U4.3 (VDD)
VBUS: C1_BAT.1, C4_USB.1, C5_USB.1, CHG_LED.A, D1.5 (VBUS), D2.2 (ANODE), MCP73831.4 (VIN), PFMF.050.1.2, Q1.1 (G), R1_PWRUSB.2, TP14.TP
VRTC: C8.1, C10_SUPERCAP.2, R_CAPACITOR.1, U3.14 (VBAT)
VUSB: J2.A4, J2.A9, J2.B4, J2.B9, PFMF.050.1.1

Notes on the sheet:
DMG2305UX-7
SD0805S020S1R0
BME688
Fromea Dragos-Florin

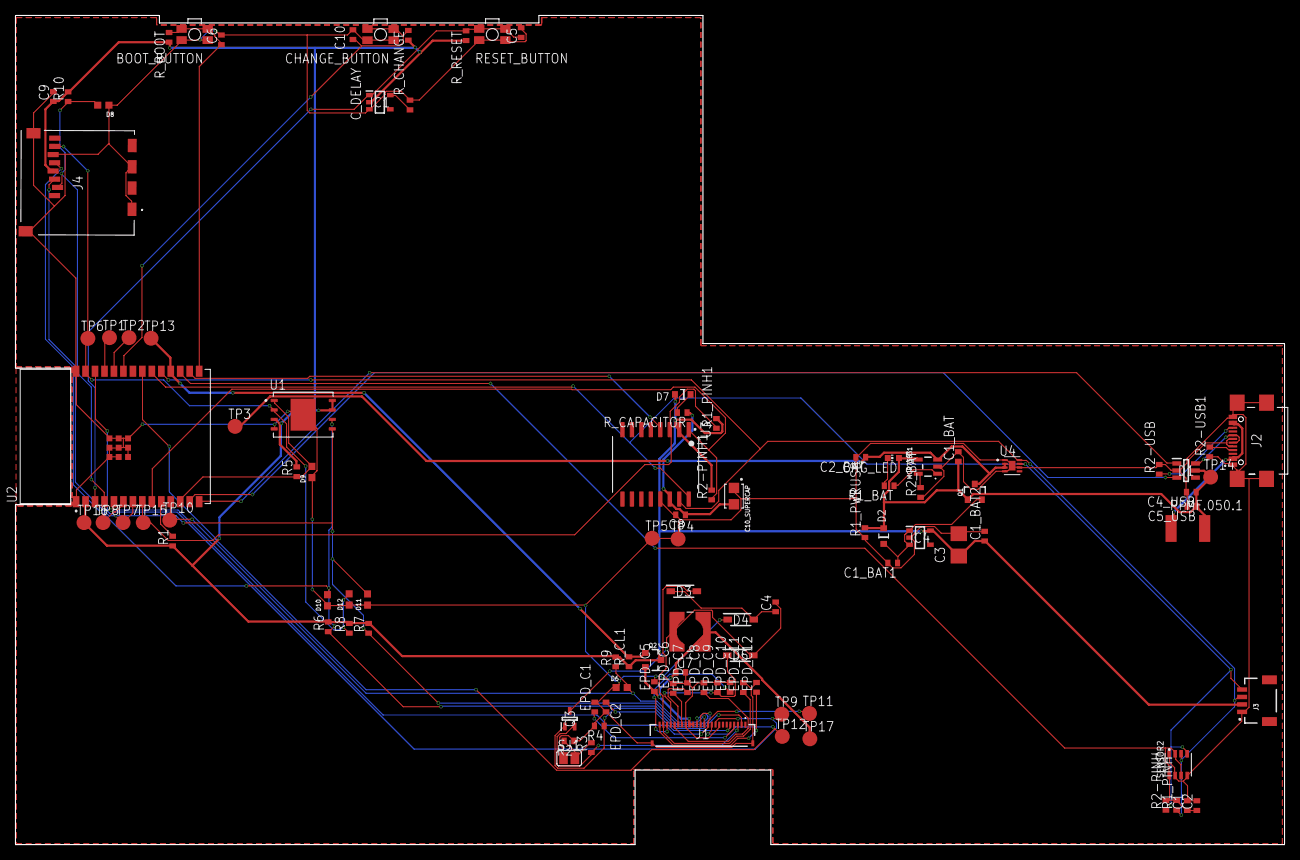
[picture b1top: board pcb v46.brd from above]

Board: 2 copper layers, 170.2 x 111.2 mm, 103 parts (0 on the bottom side), 55 nets.

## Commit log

2025-04-06 Create LICENSE
    -
2025-04-06 Update README.md
    diagram

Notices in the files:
parts and their libraries:
DeskAssistant v19 v1: COPYRIGHT: Copyright (C) 2024 Ultra Librarian. All rights reserved.
